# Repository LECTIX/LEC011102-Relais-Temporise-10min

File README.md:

# LEC011102-Relais-Temporise-10min
Fichiers sources pour le produit LEC011102

## Description du produit

Lorsque les 2 bornes BTN sont reliées via un bouton poussoir, un ILS ou équivalent, le relais reste activé pour une temporisation réglable entre 10s et 10 min.

- **ACTIVATION** Reliez les 2 bornes (avec un bouton poussoir, ILS, ou équivalent) pour enclencher le relais pour un temps réglable de 10 sec à environs 10 min.
- **RÉGLAGE** Réglez simplement la temporisation en utilisant un tournevis pour ajuster le potentiomètre.
- **ALIMENTATION** 8 – 16 V DC / AC (12V DC recommandé)
- **APPLICATIONS** Déclenchez facilement automatismes, animations et éclairages pendant un certain temps, ou après un certain délais.

## Utiliser les fichiers sources pour fabriquer le produit

Il n'est **pas nécessaire de savoir souder ou d'être bon en électronique** pour se procurer ce produit. Grâce aux fichiers sources publiés ici, vous pouvez être en mesure de faire fabriquer ce produit par un sous traitant.

### Faire fabriquer chez un sous traitant

Il est aujourd'hui possible de faire fabriquer à moindre cout des cartes électroniques. Nous recommendons [JLCPCB](https://jlcpcb.com/) si vous voulez aller au moins cher. Si vous préférez un acteur européen, [eurocircuits](https://www.eurocircuits.com/) est un des acteurs reconnus.

1. Télécherger les sources de ce produit en cliquant sur le bouton `Code`, puis `Download ZIP`.
1. Décompresser le dossier.
1. Les fichiers pour la fabrication se trouvent dans le répertoire `hardware/prod`.
1. Se connecter sur [https://cart.jlcpcb.com/quote](https://cart.jlcpcb.com/quote)
1. Cliquer sur le bouton `Add gerber file` et sélectionner le fichier `gerbers.zip`.
1. Sélectionnez la quantité de cartes que vous souhaitez dans le champs `PCB Qty`.
1. Laisser toutes les autres options par défaut, puis cliquez sur le toggle switch en face de `PCB Assembly`, et enfin sur le bouton `confirm`.
1. Une preview de la carte électronique sans les composants doit apparaitre. Cliquez sur `NEXT`.
1. Cliquez sur le bouton `Add BOM File`, puis sélectionnez le fichier `bom.csv`
1. Cliquez sur le bouton `Add CPL File`, puis sélectionnez le fichier `pos.csv`
1. **Vérifier que tous les composants sont en stock** et bien sélectionnés, puis cliquez sur `NEXT`.
1. Une preview de la carte avec ses composants apparait. Continuer le chemin en cliquant sur `NEXT`.
1. Le prix final apparait. Sélectionnez la catégorie du produit, puis cliquez sur `SAVE TO CART`.
1. Une fois sauvegardé dans votre panier, vous pouvez valider votre commande et choisir le moyen d'acheminement. Afin de ne pas avoir à se préoccuper des frais de douane, nous vous conseillons de choisir une méthode d'expédition DDP.

Vous receverez vos cartes sous 1 à 3 semaines. 

**Nous ne sommes en aucun cas responsables des cartes qui arriveraient défectueuses ou non fonctionnelles.**

### Modifications des fichiers sources

Installez kicad 6 (ou version supérieure), et ouvrez le fichier LEC011102.kicad_pro

### Regénérer les fichiers gerber, BOM, et position (Optionnel)

Peut se faire simplement en utilisant kikit :

```
cd hardware
docker run --rm -w /kikit -v $PWD:/kikit yaqwsx/kikit kikit fab jlcpcb --assembly --no-drc --schematic LEC011102.kicad_sch --field LCSC --corrections JLCPCB_CORRECTION --nametemplate LEC011102_{} LEC011102.kicad_pcb prod/

```
## Notices

Il n'existe pas de manuel spécifique à ce produit, mais vous pouvez retrouver le manuel du relais temporisé 3 min qui est très similaire.

[Manuel FR](https://github.com/LECTIX/LEC011001-Relais-Temporise-3min30/blob/main/docs/manual_fr.pdf)

## License
Tous nos fichiers sont plubliés sous la license CERN Open Hardware Licence Version 2 - Strongly Reciprocal

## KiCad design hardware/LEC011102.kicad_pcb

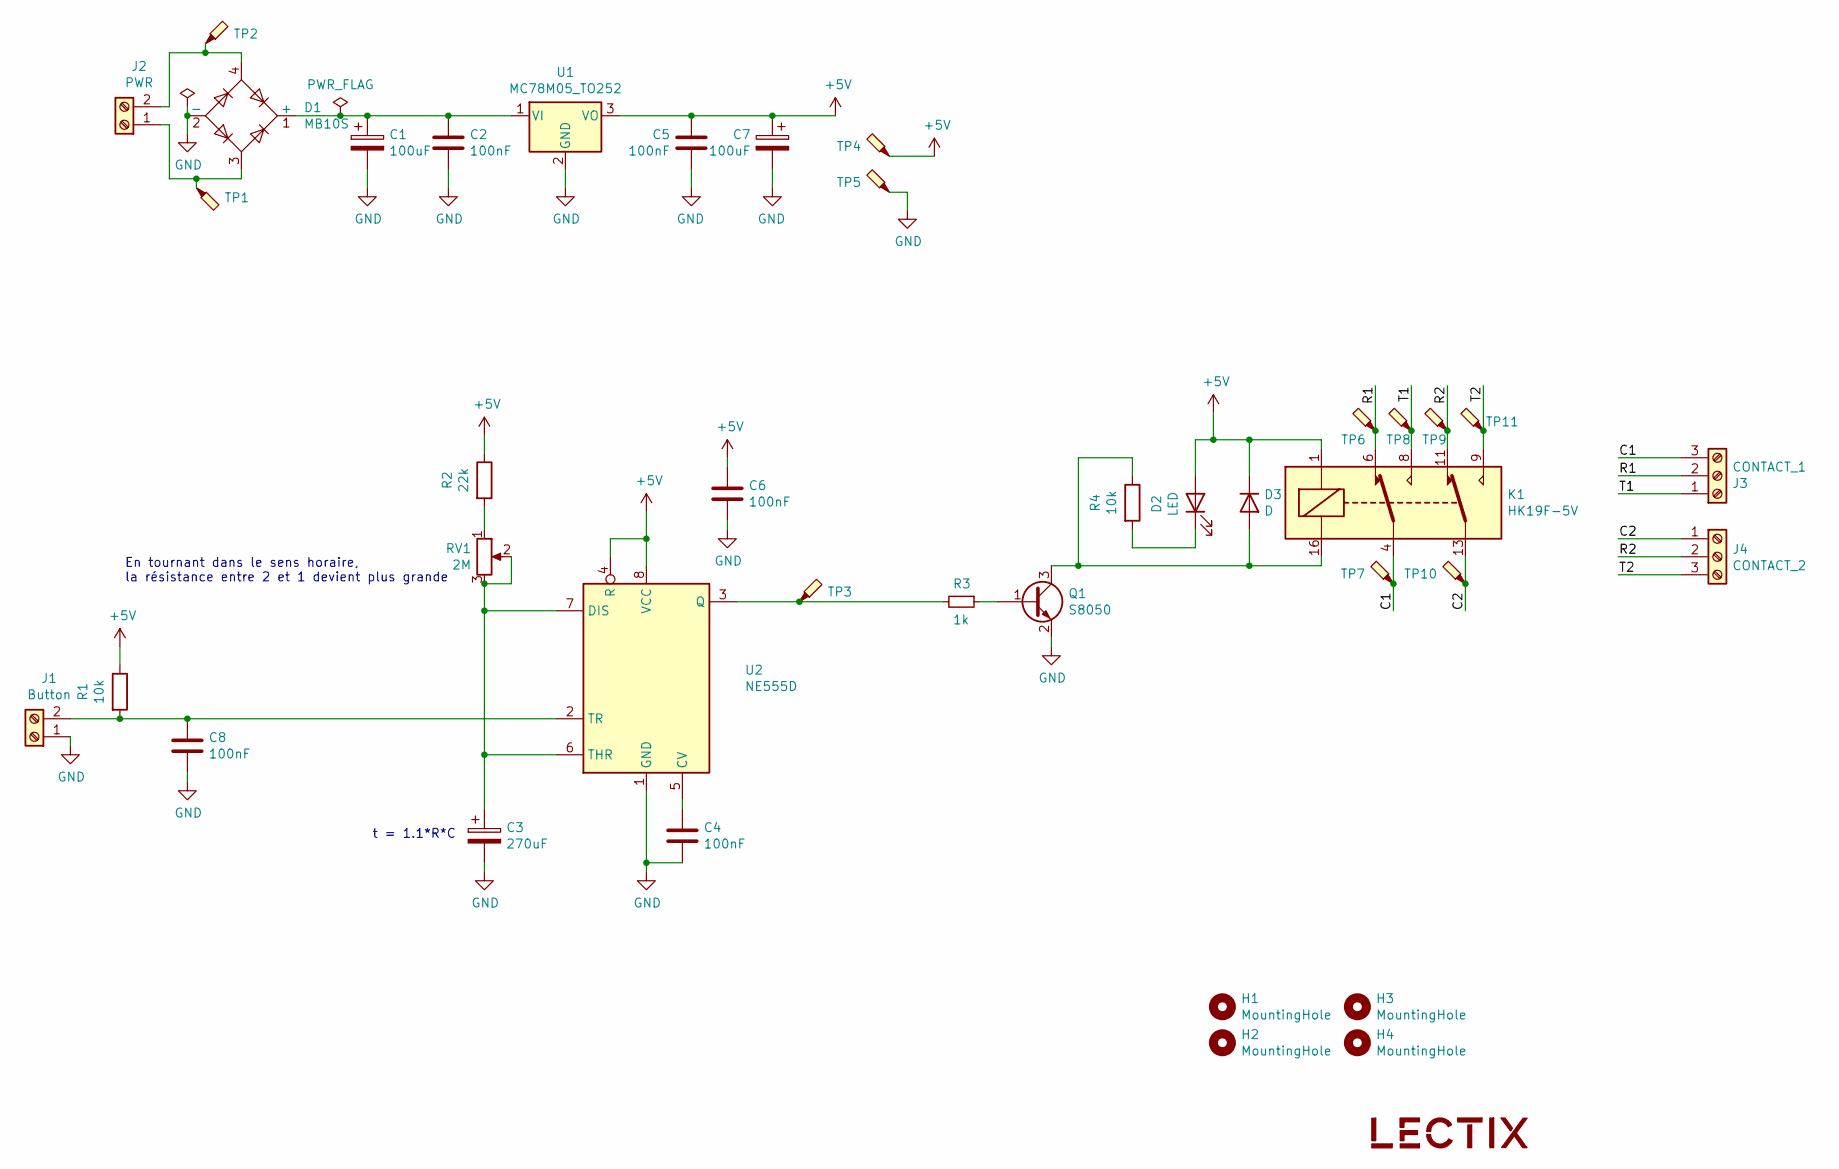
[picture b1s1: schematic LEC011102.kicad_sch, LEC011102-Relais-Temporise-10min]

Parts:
C1, C7: 100uF; CP_Elec_6.3x5.8; MPN VZT101M1VTR-0606; LCSC C249982
C2, C4, C5, C6, C8: 100nF; C_0603_1608Metric; MPN CC0603KRX7R9BB104; LCSC C14663
C3: 270uF; CP_Radial_D8.0mm_P3.50mm; MPN FP-016RE271M-NUCGL-FE; LCSC C225856
D1: MB10S; TO-269AA; MPN MB10S; LCSC C2488
D2: LED; LED_0603_1608Metric; MPN 19-217/GHC-YR1S2/3T; LCSC C72043
D3: D; D_SMA; MPN M7; LCSC C95872
H1, H2, H3, H4: MountingHole; MountingHole_3.2mm_M3; MPN DNP
J1: Button; TerminalBlock_bornier-2_P5.08mm-blue; MPN DB301V-5.0-2P-BU-P; LCSC C430621
J2: PWR; TerminalBlock_bornier-2_P5.08mm-green; MPN DB126V-5.0-2P-GN; LCSC C395849
J3: CONTACT_1; TerminalBlock_bornier-3_P5.08mm-blue; MPN DB301V-5.0-3P-BU-P; LCSC C430620
J4: CONTACT_2; TerminalBlock_bornier-3_P5.08mm-blue; MPN DB301V-5.0-3P-BU-P; LCSC C430620
K1: HK19F-5V; Relay_DPDT_HK19F; MPN HK19F-DC5V-SHG-Y; LCSC C54512
LOGO1: logo_lectix_25mm; Logo_10mm; MPN DNP
Q1: S8050; SOT-23; MPN S8050; LCSC C2146
R1, R4: 10k; R_0603_1608Metric; MPN 0603WAF1002T5E; LCSC C25804
R2: 22k; R_0603_1608Metric; MPN 0603WAF2202T5E; LCSC C31850
R3: 1k; R_0603_1608Metric; MPN 0603WAF1001T5E; LCSC C21190
RV1: 2M; Potentiometer_3296W_Vertical; MPN 3296W-1-205; LCSC C118923
TP1, TP2, TP3, TP4, TP5, TP6, TP7, TP8, TP9, TP10, TP11: TestPoint_Probe; TestPoint_Pad_D1.5mm; MPN DNP
U1: MC78M05_TO252; TO-252-2; LCSC C58069
U2: NE555D; SOIC-8_3.9x4.9mm_P1.27mm; MPN NE555D; LCSC C7593

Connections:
+5V: C5.1, C6.1, C7.1, D2.2 (A), D3.1 (K), K1.1, R1.1, R2.1, TP4.1, U1.3 (VO), U2.4 (R), U2.8 (VCC)
/C1: J3.3, K1.4, TP7.1
/C2: J4.1, K1.13, TP10.1
/R1: J3.2, K1.6, TP6.1
/R2: J4.2, K1.11, TP9.1
/T1: J3.1, K1.8, TP8.1
/T2: J4.3, K1.9, TP11.1
GND: C1.2, C2.2, C3.2, C4.2, C5.2, C6.2, C7.2, C8.2, D1.2 (-), J1.1, Q1.2 (E), TP5.1, U1.2 (GND), U2.1 (GND)
unnamed: C1.1, C2.1, D1.1 (+), U1.1 (VI)
unnamed: C3.1, RV1.2, RV1.3, U2.6 (THR), U2.7 (DIS)
unnamed: C4.1, U2.5 (CV)
unnamed: D1.3, J2.1, TP1.1
unnamed: D1.4, J2.2, TP2.1
unnamed: D2.1 (K), R4.2
unnamed: D3.2 (A), K1.16, Q1.3 (C), R4.1
unnamed: C8.1, J1.2, R1.2, U2.2 (TR)
unnamed: Q1.1 (B), R3.1
unnamed: R2.2, RV1.1
unnamed: R3.2, TP3.1, U2.3 (Q)

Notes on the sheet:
t = 1.1*R*C
En tournant dans le sens horaire, la résistance entre 2 et 1 devient plus grande

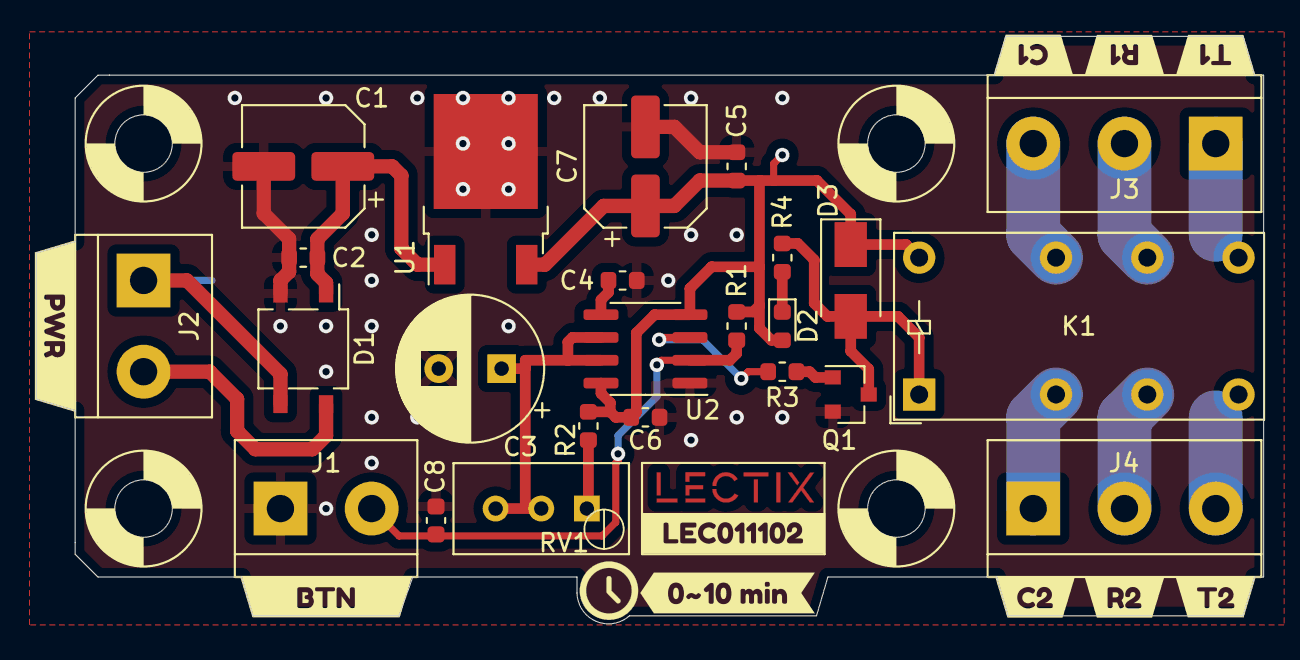
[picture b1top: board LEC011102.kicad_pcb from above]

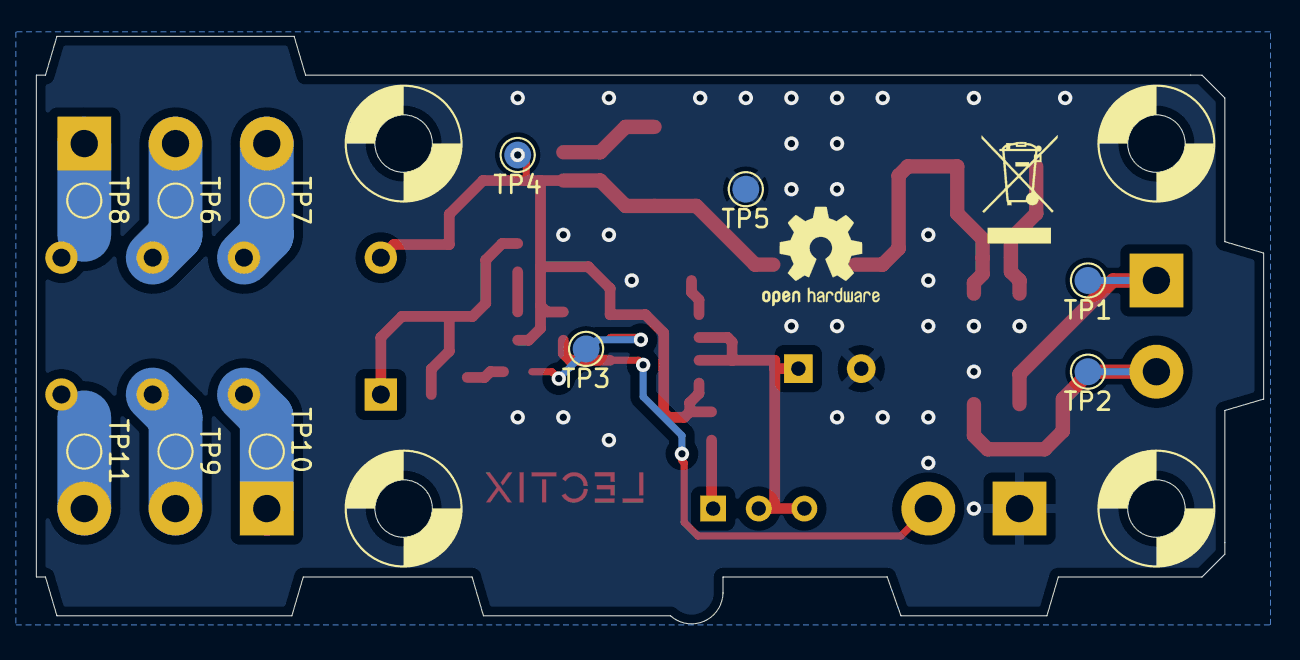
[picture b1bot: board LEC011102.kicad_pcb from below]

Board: 2 copper layers, 68.3 x 32.7 mm, 50 parts (11 on the bottom side), 19 nets.

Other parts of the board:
kibuzzard-621F68B9: G***; kibuzzard-621F68B9
kibuzzard-621F6901: G***; kibuzzard-621F6901
kibuzzard-6223B0D3: G***; kibuzzard-6223B0D3
kibuzzard-6223B0EB: G***; kibuzzard-6223B0EB
kibuzzard-6223B1FE: G***; kibuzzard-6223B1FE
kibuzzard-6223B13F: G***; kibuzzard-6223B13F
kibuzzard-6223B18A: G***; kibuzzard-6223B18A
kibuzzard-6223B135: G***; kibuzzard-6223B135
kibuzzard-6223B147: G***; kibuzzard-6223B147
kibuzzard-6224C48E: G***; kibuzzard-6224C48E

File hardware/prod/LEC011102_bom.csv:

Comment,Designator,Footprint,LCSC
100uF,"C1,C7",0_capacitors:CP_Elec_6.3x5.8,C249982
100nF,"C2,C4,C5,C6,C8",Capacitor_SMD:C_0603_1608Metric,C14663
270uF,C3,Capacitor_THT:CP_Radial_D8.0mm_P3.50mm,C225856
MB10S,D1,Package_TO_SOT_SMD:TO-269AA,C2488
LED,D2,LED_SMD:LED_0603_1608Metric,C72043
D,D3,Diode_SMD:D_SMA,C95872
Button,J1,0_connectors:TerminalBlock_bornier-2_P5.08mm-blue,C430621
PWR,J2,0_connectors:TerminalBlock_bornier-2_P5.08mm-green,C395849
CONTACT_1,J3,0_connectors:TerminalBlock_bornier-3_P5.08mm-blue,C430620
CONTACT_2,J4,0_connectors:TerminalBlock_bornier-3_P5.08mm-blue,C430620
HK19F-5V,K1,0_relays:Relay_DPDT_HK19F,C54512
S8050,Q1,Package_TO_SOT_SMD:SOT-23,C2146
10k,"R1,R4",Resistor_SMD:R_0603_1608Metric,C25804
22k,R2,Resistor_SMD:R_0603_1608Metric,C31850
1k,R3,Resistor_SMD:R_0603_1608Metric,C21190
2M,RV1,0_potentiometers:Potentiometer_3296W_Vertical,C118923
MC78M05_TO252,U1,Package_TO_SOT_SMD:TO-252-2,C58069
NE555D,U2,Package_SO:SOIC-8_3.9x4.9mm_P1.27mm,C7593

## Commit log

2023-03-26 Add source files
2023-03-26 Add prod files
2023-03-26 Add pdf schematic file
2023-03-26 update product manual link

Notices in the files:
hardware/LEC011102.kicad_sch:
CERN-OHL-S-2.0 license
